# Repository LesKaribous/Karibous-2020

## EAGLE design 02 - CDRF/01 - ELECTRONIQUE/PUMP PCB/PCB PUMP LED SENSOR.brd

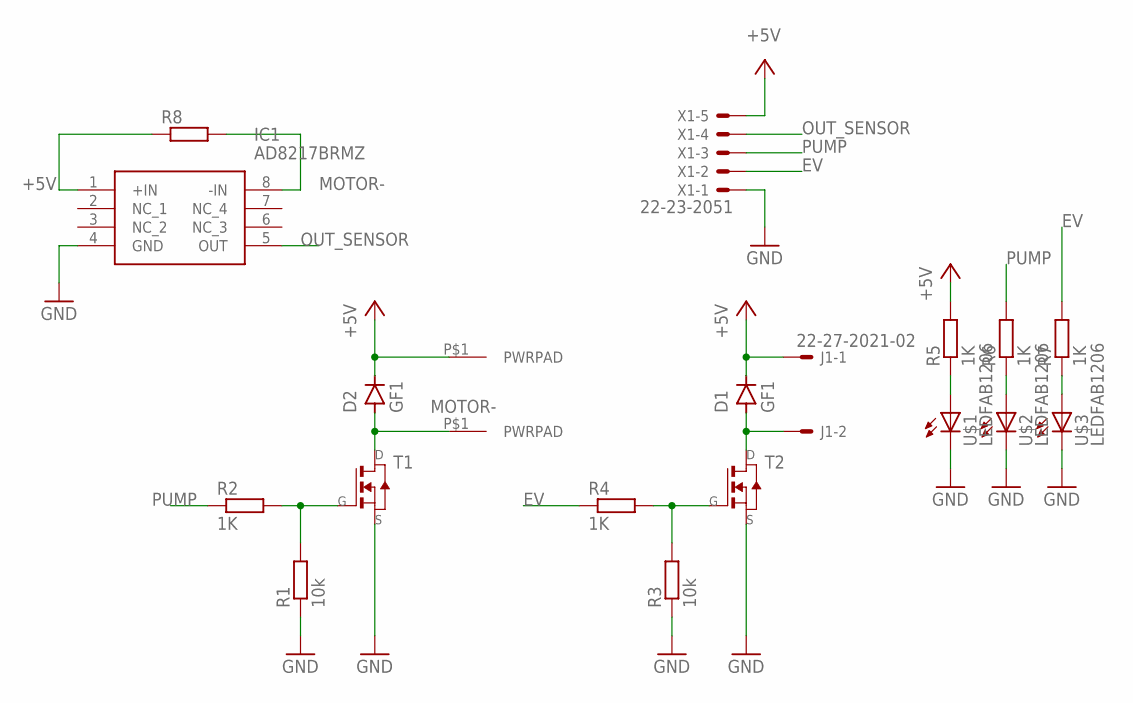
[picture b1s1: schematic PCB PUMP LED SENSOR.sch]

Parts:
D1, D2: GF1; SMA-DO214AC
IC1: AD8217BRMZ; SOP65P490X110-8N
J1: 22-27-2021-02; 6410-02
J3, J4: PWRPAD2-5MM; PWRPAD_2-5MM
R1, R3: 10k; R1206
R2, R4, R5, R6, R7: 1K; R1206
R8: R-EU_R0805; R0805
T1, T2: NMOSFETSOT23; SOT-23
U$1, U$2, U$3: LEDFAB1206; LED1206FAB
X1: 22-23-2051

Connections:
+5V: D1.K (C), D2.K (C), IC1.1 (+IN), J1.1, J4.P$1, R5.2, R8.1, X1.5
EV: R4.1, R7.2, X1.2
GND: IC1.4 (GND), R1.1, R3.1, T1.2 (S), T2.2 (S), U$1.2 (C), U$2.2 (C), U$3.2 (C), X1.1
MOTOR-: D2.A, IC1.8 (-IN), J3.P$1, R8.2, T1.1 (D)
unnamed: D1.A, J1.2, T2.1 (D)
unnamed: R1.2, R2.2, T1.3 (G)
unnamed: R3.2, R4.2, T2.3 (G)
unnamed: R5.1, U$1.1 (A)
unnamed: R6.1, U$2.1 (A)
unnamed: R7.1, U$3.1 (A)
OUT_SENSOR: IC1.5 (OUT), X1.4
PUMP: R2.1, R6.2, X1.3

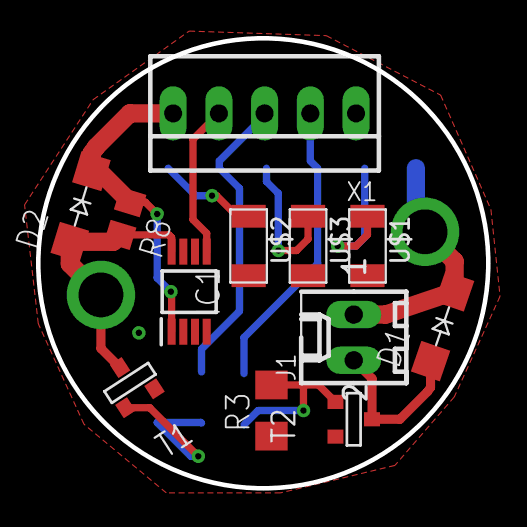
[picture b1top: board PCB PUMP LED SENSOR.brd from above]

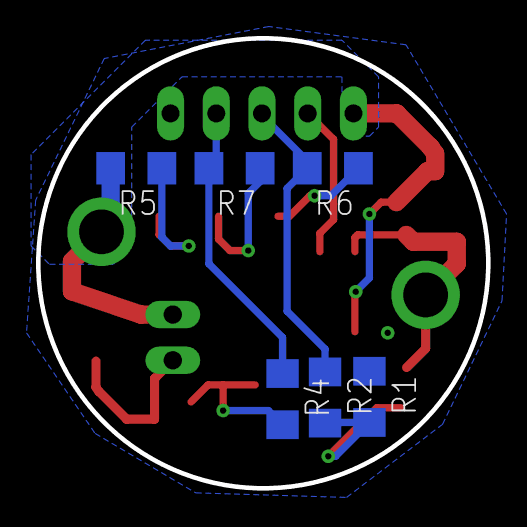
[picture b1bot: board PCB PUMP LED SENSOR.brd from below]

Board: 2 copper layers, 25.0 x 25.0 mm, 20 parts (6 on the bottom side), 12 nets.

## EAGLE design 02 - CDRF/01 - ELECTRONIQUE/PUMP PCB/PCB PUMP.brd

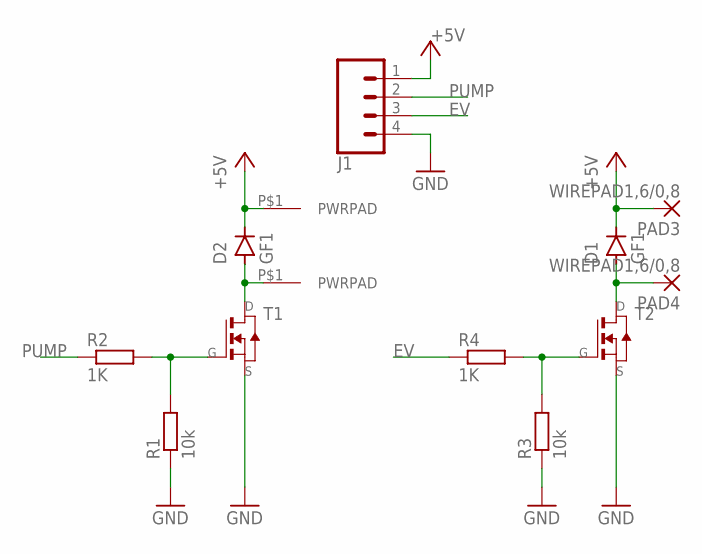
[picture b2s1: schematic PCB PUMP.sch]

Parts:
D1, D2: GF1; SMA-DO214AC
J1: CONN_04POLAR; MOLEX-1X4
J3, J4: PWRPAD2-5MM; PWRPAD_2-5MM
PAD3, PAD4: WIREPAD1,6/0,8; 1,6/0,8
R1, R3: 10k; R1206
R2, R4: 1K; R1206
T1, T2: NMOSFETSOT23; SOT-23

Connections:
+5V: D1.K (C), D2.K (C), J1.1, J4.P$1, PAD3.1
EV: J1.3, R4.1
GND: J1.4, R1.1, R3.1, T1.2 (S), T2.2 (S)
unnamed: D1.A, PAD4.1, T2.1 (D)
unnamed: D2.A, J3.P$1, T1.1 (D)
unnamed: R1.2, R2.2, T1.3 (G)
unnamed: R3.2, R4.2, T2.3 (G)
PUMP: J1.2, R2.1

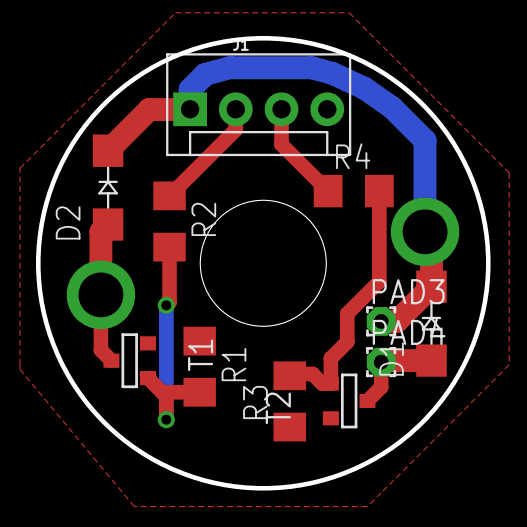
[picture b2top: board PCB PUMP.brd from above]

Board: 2 copper layers, 25.0 x 25.0 mm, 13 parts (0 on the bottom side), 8 nets.

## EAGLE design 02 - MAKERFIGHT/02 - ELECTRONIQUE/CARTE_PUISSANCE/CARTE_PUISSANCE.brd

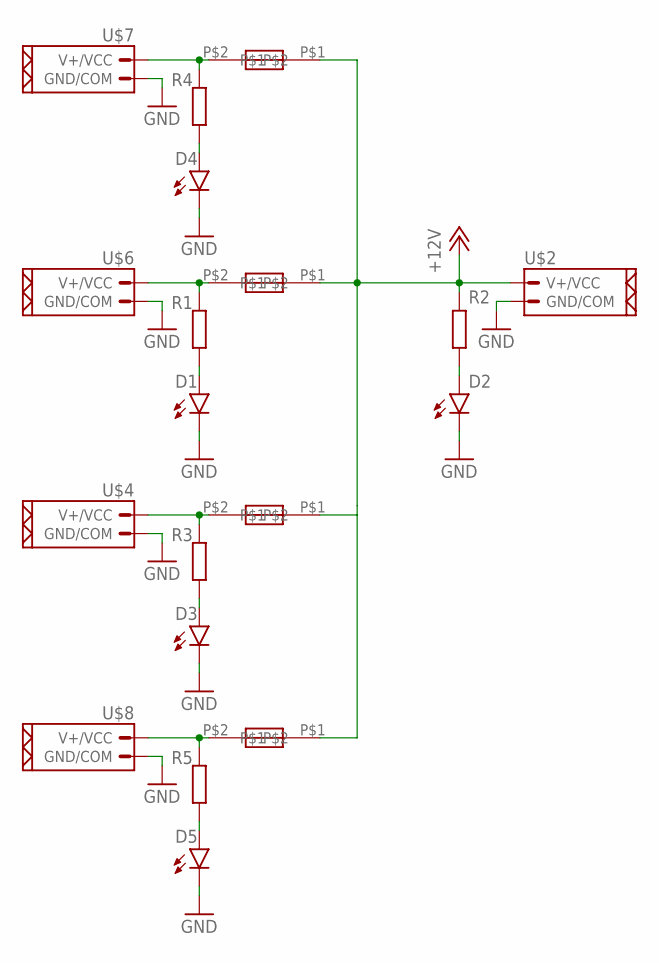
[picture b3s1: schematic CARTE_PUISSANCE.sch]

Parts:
D1, D2, D3, D4, D5: LED5MM; LED_5MM
R1, R2, R3, R4, R5: R-EU_0204/7; 0204/7
U$1, U$3, U$5, U$9: AUTOMOTIVE_FUSE
U$2, U$4, U$6, U$7, U$8: CONN_02_PUIXT60; XT60

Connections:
+12V: R2.2, U$1.P$1, U$2.P$1 (V+/VCC), U$3.P$1, U$5.P$1, U$9.P$1
GND: D1.K (C), D2.K (C), D3.K (C), D4.K (C), D5.K (C), U$2.P$2 (GND/COM), U$4.P$2 (GND/COM), U$6.P$2 (GND/COM), U$7.P$2 (GND/COM), U$8.P$2 (GND/COM)
unnamed: R1.2, U$3.P$2, U$6.P$1 (V+/VCC)
unnamed: D1.A, R1.1
unnamed: R5.2, U$8.P$1 (V+/VCC), U$9.P$2
unnamed: D2.A, R2.1
unnamed: R3.2, U$4.P$1 (V+/VCC), U$5.P$2
unnamed: D3.A, R3.1
unnamed: R4.2, U$1.P$2, U$7.P$1 (V+/VCC)
unnamed: D4.A, R4.1
unnamed: D5.A, R5.1

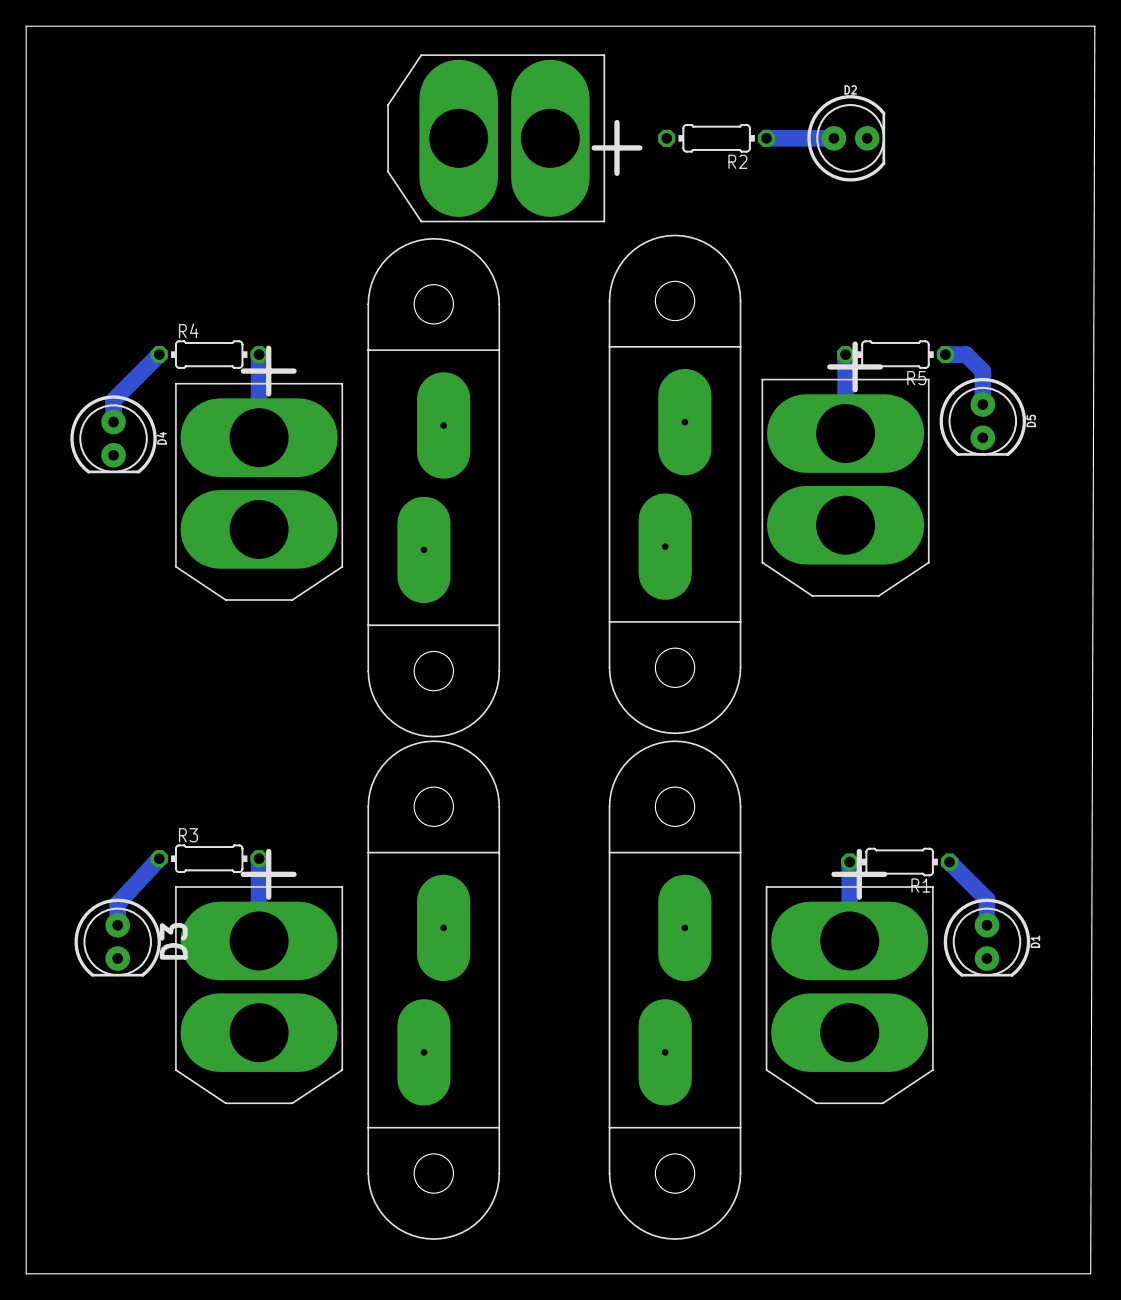
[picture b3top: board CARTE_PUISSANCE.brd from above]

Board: 2 copper layers, 81.6 x 95.2 mm, 19 parts (0 on the bottom side), 11 nets.
